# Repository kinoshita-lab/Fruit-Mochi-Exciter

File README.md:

# Fruit Mochi Exciter

[日本語](README.ja.md)

Mochi(Fruit Mochi) is a famous Japanese sweets, which (from my perspective) looks like trigger pads what DJs/Musicians doing some kind of cool activities!
This product enables mochi lighting to derive full potential of the mochi itself...!

<br />

## Features

- Can change tempo via potentiometer

## Kit Contents

- Pre-assembled circuit board
- M3 12mm screws: 4pcs.
- M3 nuts: 4pcs.
- Acrylic boards(1, 2, 3)
- Rubber feets: 4pcs.

## What you will need

- USB Type-C cable, with connected to the power source(AC adapter, PC, etc.)
- Screwdriver
- Fruit Mochi: 15 pcs.

## How to assemble

- Remove the sealing paper on the accrylic boards.
- Put board 1 on the circuit board.
- Put board 2 on the board 1
- Put board 3 on the board 2
- Fix all with 12mm screws and nuts.

## How to use

- Place mochis on the board.
- Start lighting by connecting the USB.
- Enjoy!

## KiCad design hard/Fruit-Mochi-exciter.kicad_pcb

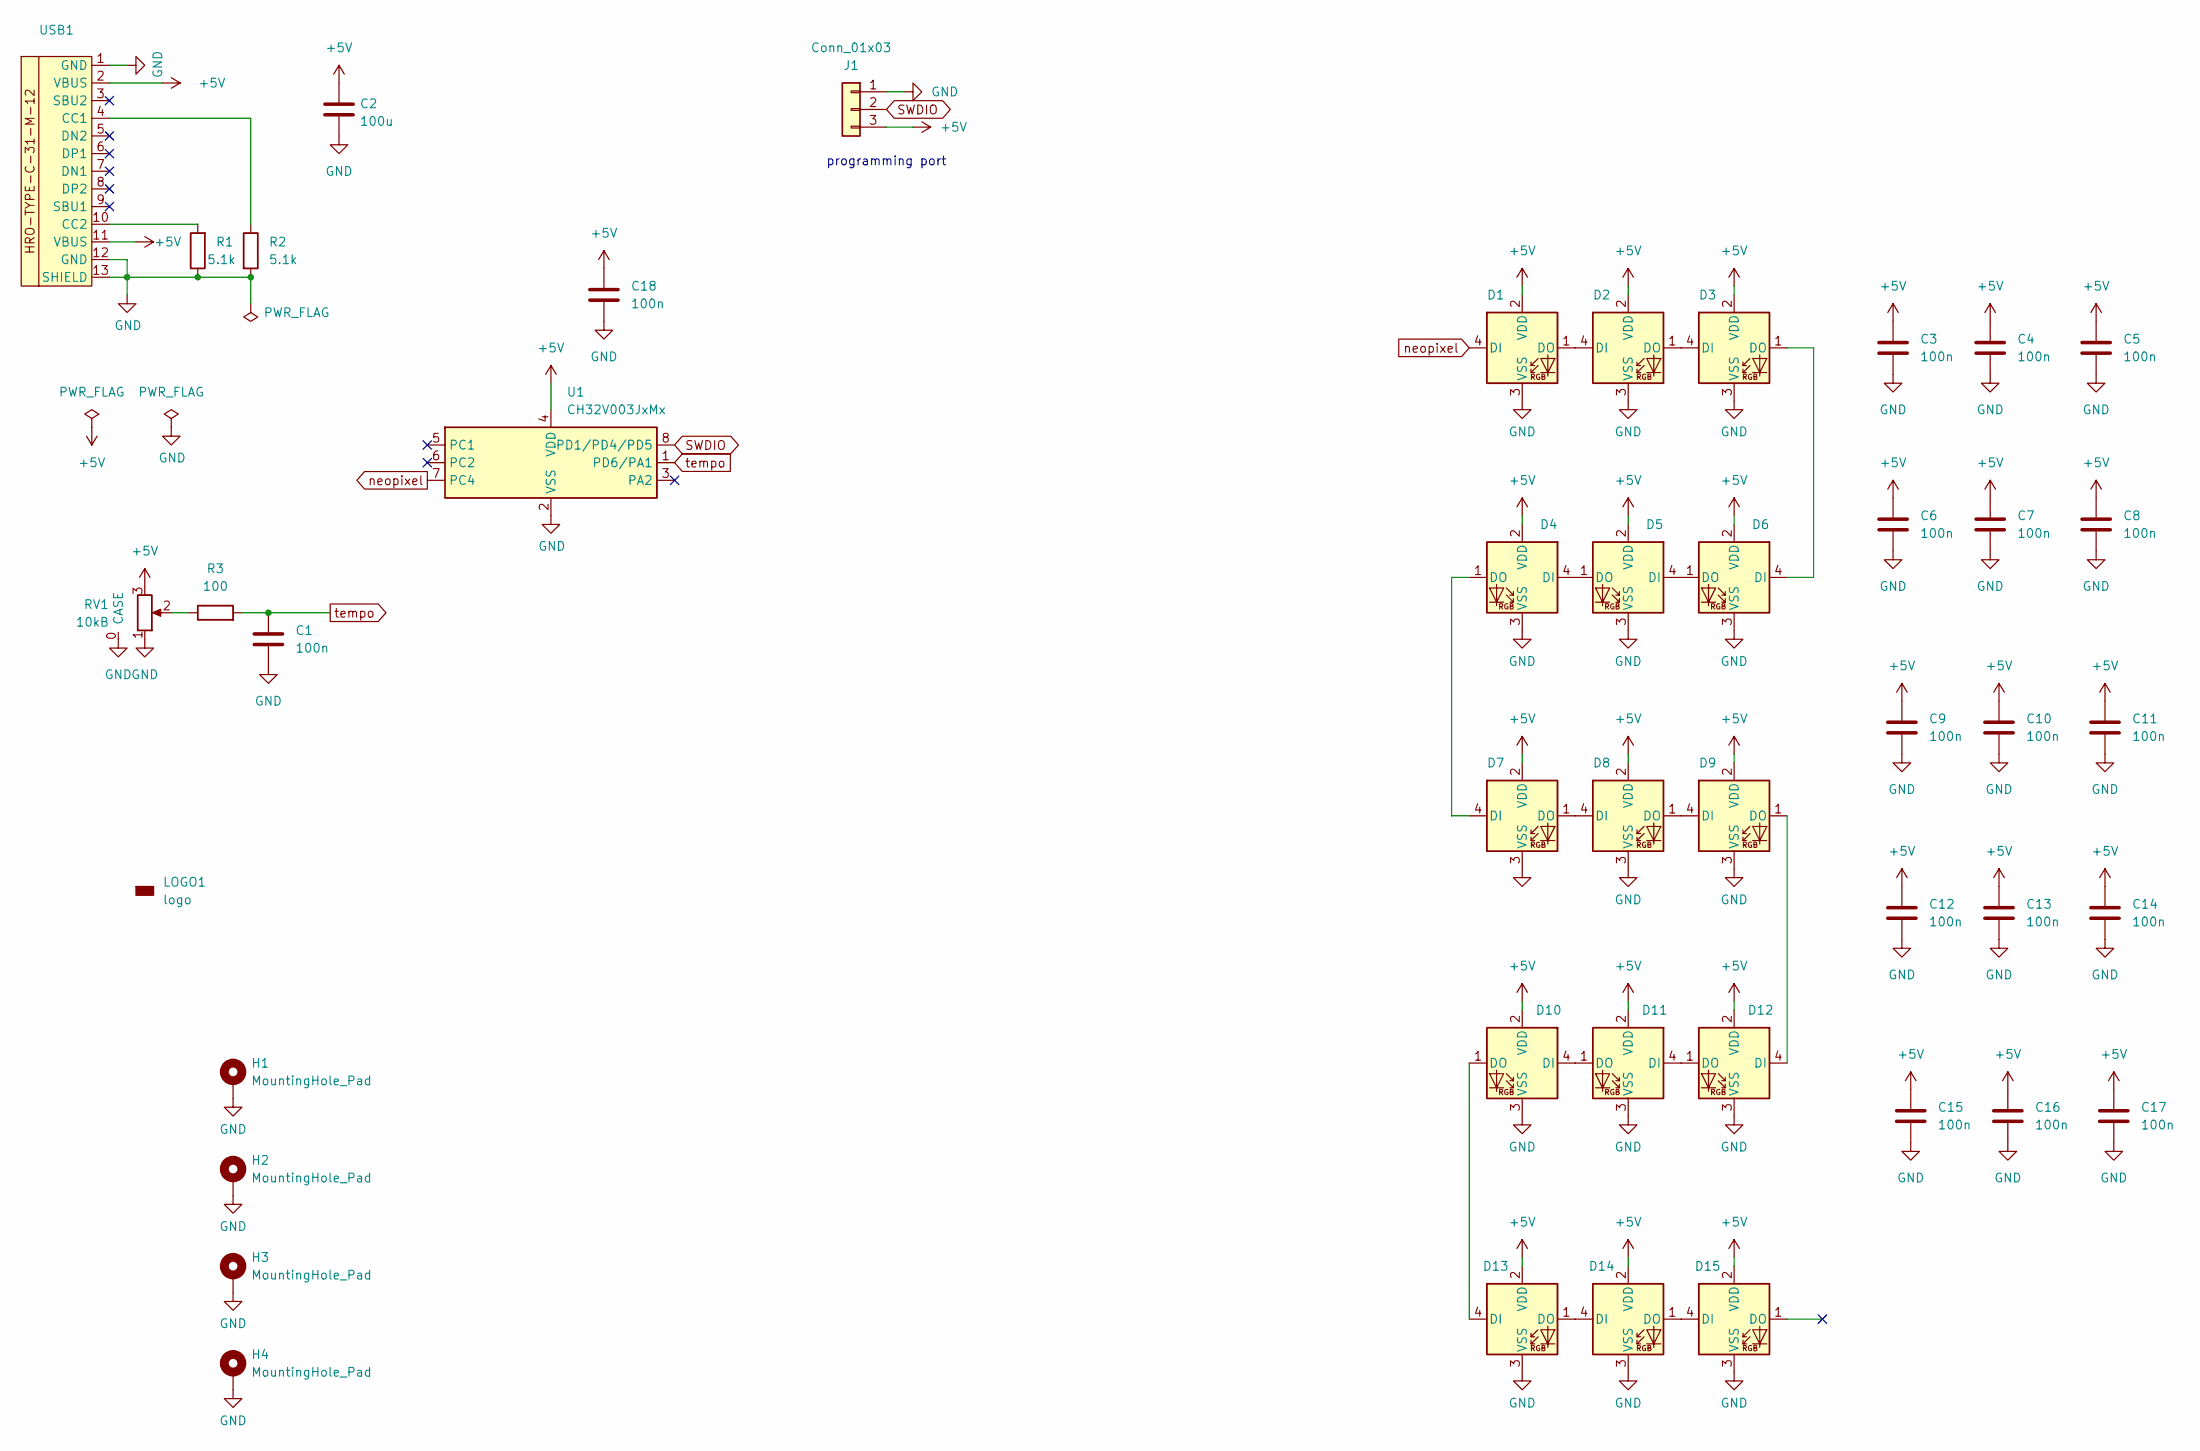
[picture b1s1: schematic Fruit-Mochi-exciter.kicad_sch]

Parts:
C1, C3, C4, C5, C6, C7, C8, C9, C10, C11, C12, C13, C14, C15, C16, C17, C18: 100n; C_0402_1005Metric_Pad0.74x0.62mm_HandSolder; LCSC C1525
C2: 100u; C_1206_3216Metric_Pad1.33x1.80mm_HandSolder; LCSC C312983
D1, D2, D3, D4, D5, D6, D7, D8, D9, D10, D11, D12, D13, D14, D15: LED_NeoPixel_XL-1615RGBC-WS2812B; LCSC C5349954
H1, H2, H3, H4: MountingHole_Pad; MountingHole_3.2mm_M3_Pad
J1: Conn_01x03; PinHeader_1x03_P2.54mm_Vertical
LOGO1: logo; kinoshita-logo_simplified_300dpi
R1, R2: 5.1k; R_0402_1005Metric; LCSC C25905
R3: 100; R_0402_1005Metric_Pad0.72x0.64mm_HandSolder; LCSC C106232
RV1: 10kB; Potentiometer_Alps_RK09K_Horizontal_CORRECTED; LCSC C470294
U1: CH32V003JxMx; SOP-8_3.9x4.9mm_P1.27mm; LCSC C5346354
USB1: HRO TYPE-C-31-M-08A; LCSC C2848616

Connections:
+5V: C2.1, C3.1, C4.1, C5.1, C6.1, C7.1, C8.1, C9.1, C10.1, C11.1, C12.1, C13.1, C14.1, C15.1, C16.1, C17.1, C18.1, D1.2 (VDD), D2.2 (VDD), D3.2 (VDD), D4.2 (VDD), D5.2 (VDD), D6.2 (VDD), D7.2 (VDD), D8.2 (VDD), D9.2 (VDD), D10.2 (VDD), D11.2 (VDD), D12.2 (VDD), D13.2 (VDD), D14.2 (VDD), D15.2 (VDD), J1.3, RV1.3, U1.4 (VDD), USB1.2 (VBUS), USB1.11 (VBUS)
GND: C1.2, C2.2, C3.2, C4.2, C5.2, C6.2, C7.2, C8.2, C9.2, C10.2, C11.2, C12.2, C13.2, C14.2, C15.2, C16.2, C17.2, C18.2, D1.3 (VSS), D2.3 (VSS), D3.3 (VSS), D4.3 (VSS), D5.3 (VSS), D6.3 (VSS), D7.3 (VSS), D8.3 (VSS), D9.3 (VSS), D10.3 (VSS), D11.3 (VSS), D12.3 (VSS), D13.3 (VSS), D14.3 (VSS), D15.3 (VSS), H1.1, H2.1, H3.1, H4.1, J1.1, R1.1, R2.2, RV1.0 (CASE), RV1.1, U1.2 (VSS), USB1.1 (GND), USB1.12 (GND), USB1.13 (SHIELD)
unnamed: D1.1 (DO), D2.4 (DI)
unnamed: D2.1 (DO), D3.4 (DI)
unnamed: D3.1 (DO), D6.4 (DI)
unnamed: D4.4 (DI), D5.1 (DO)
unnamed: D4.1 (DO), D7.4 (DI)
unnamed: D5.4 (DI), D6.1 (DO)
unnamed: D7.1 (DO), D8.4 (DI)
unnamed: D8.1 (DO), D9.4 (DI)
unnamed: D10.4 (DI), D11.1 (DO)
unnamed: D10.1 (DO), D13.4 (DI)
unnamed: D11.4 (DI), D12.1 (DO)
unnamed: D9.1 (DO), D12.4 (DI)
unnamed: D13.1 (DO), D14.4 (DI)
unnamed: D14.1 (DO), D15.4 (DI)
unnamed: R3.1, RV1.2
unnamed: R2.1, USB1.4 (CC1)
unnamed: R1.2, USB1.10 (CC2)
SWDIO: J1.2, U1.8 (PD1/PD4/PD5)
neopixel: D1.4 (DI), U1.7 (PC4)
tempo: C1.1, R3.2, U1.1 (PD6/PA1)

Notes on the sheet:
programming port

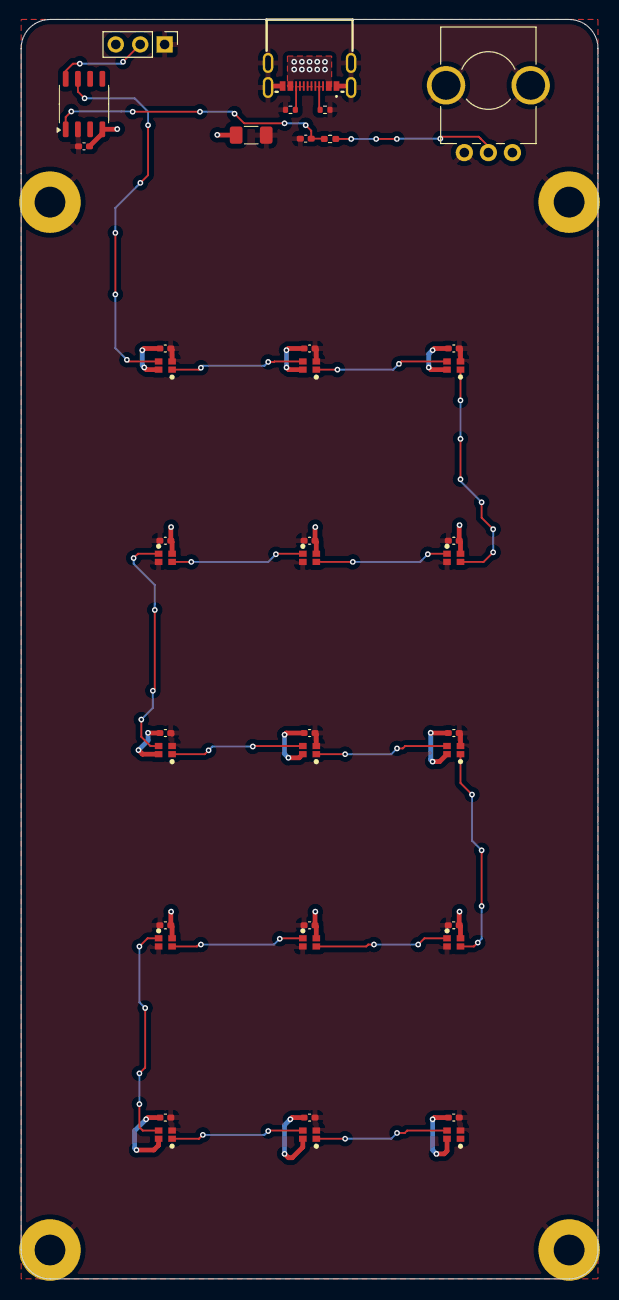
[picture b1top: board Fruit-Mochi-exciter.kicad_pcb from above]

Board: 2 copper layers, 60.0 x 131.0 mm, 45 parts (1 on the bottom side), 22 nets.

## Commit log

2024-12-19 add pcb design
2024-12-21 add soft
2024-12-21 move pcb design into hard folder
2024-12-23 Add Readme(En/Ja)
2024-12-23 Create LICENSE
2024-12-23 README.md の更新
